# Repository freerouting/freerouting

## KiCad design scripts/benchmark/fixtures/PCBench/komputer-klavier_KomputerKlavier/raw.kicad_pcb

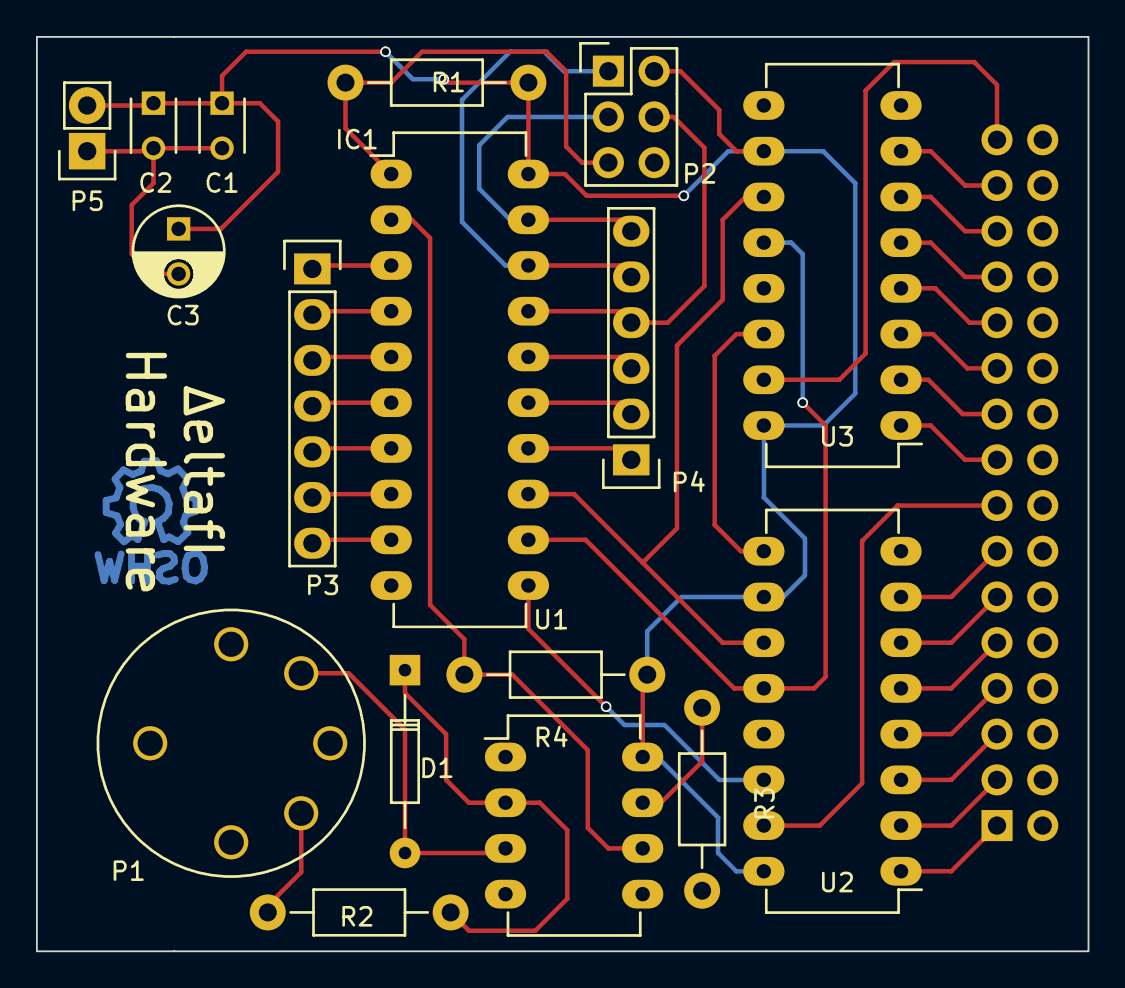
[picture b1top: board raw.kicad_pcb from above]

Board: 2 copper layers, 58.4 x 50.8 mm, 18 parts (1 on the bottom side), 41 nets.

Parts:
C1, C2: 100nf; C_Disc_D3_P2.5
C3: 1uf; C_Radial_D5_L6_P2.5
D1: 1N4148; Diode_DO-35_SOD27_Horizontal_RM10
IC1: ATTINY4313-P; DIP-20_W7.62mm_LongPads
P1: DIN_5
P2: CONN_02X03; Pin_Header_Straight_2x03
P3: CONN_01X07; Pin_Header_Straight_1x07
P4: CONN_01X06; Pin_Header_Straight_1x06
P5: CONN_01X02; Pin_Header_Straight_1x02
P6: CONN_02X16; Pin_Header_Straight_2x16
R1: 10k; Resistor_Horizontal_RM10mm
R2: 220; Resistor_Horizontal_RM10mm
R3: 1k; Resistor_Horizontal_RM10mm
R4: 470; Resistor_Horizontal_RM10mm
U1: 6N136; DIP-8_W7.62mm_LongPads
U2, U3: 74HC595; DIP-16_W7.62mm_LongPads

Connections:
GND: C1.2, C2.2, C3.2, IC1.10, P2.6, P5.1, P6.2, P6.4, P6.6, P6.8, P6.10, P6.12, P6.14, P6.16, P6.18, P6.20, P6.22, P6.24, P6.26, P6.28, P6.30, P6.32, R3.2, U1.5, U2.8, U2.13, U3.8, U3.13
unnamed: D1.1, R2.1, U1.2
unnamed: D1.2, P1.5, U1.3
unnamed: IC1.1, P2.5, R1.2
unnamed: IC1.2, R4.2, U1.6
unnamed: IC1.3, P3.1
unnamed: IC1.4, P3.2
unnamed: IC1.5, P3.3
unnamed: IC1.6, P3.4
unnamed: IC1.7, P3.5
unnamed: IC1.8, P3.6
unnamed: IC1.9, P3.7
unnamed: IC1.11, U2.14
unnamed: IC1.12, U2.12, U3.12
unnamed: IC1.13, U2.11, U3.11
unnamed: IC1.14, P4.1
unnamed: IC1.15, P4.2
unnamed: IC1.16, P4.3
unnamed: IC1.17, P2.4, P4.4
unnamed: IC1.18, P2.1, P4.5
unnamed: IC1.19, P2.3, P4.6
unnamed: P1.4, R2.2
unnamed: P6.1, U2.1
unnamed: P6.3, U2.2
unnamed: P6.5, U2.3
unnamed: P6.7, U2.4
unnamed: P6.9, U2.5
unnamed: P6.11, U2.6
unnamed: P6.13, U2.7
unnamed: P6.15, U2.15
unnamed: P6.17, U3.1
unnamed: P6.19, U3.2
unnamed: P6.21, U3.3
unnamed: P6.23, U3.4
unnamed: P6.25, U3.5
unnamed: P6.27, U3.6
unnamed: P6.29, U3.7
unnamed: P6.31, U3.15
unnamed: R3.1, U1.7
unnamed: U2.9, U3.14
VCC: C1.1, C2.1, C3.1, IC1.20, P2.2, P5.2, R1.1, R4.1, U1.8, U2.10, U2.16, U3.10, U3.16

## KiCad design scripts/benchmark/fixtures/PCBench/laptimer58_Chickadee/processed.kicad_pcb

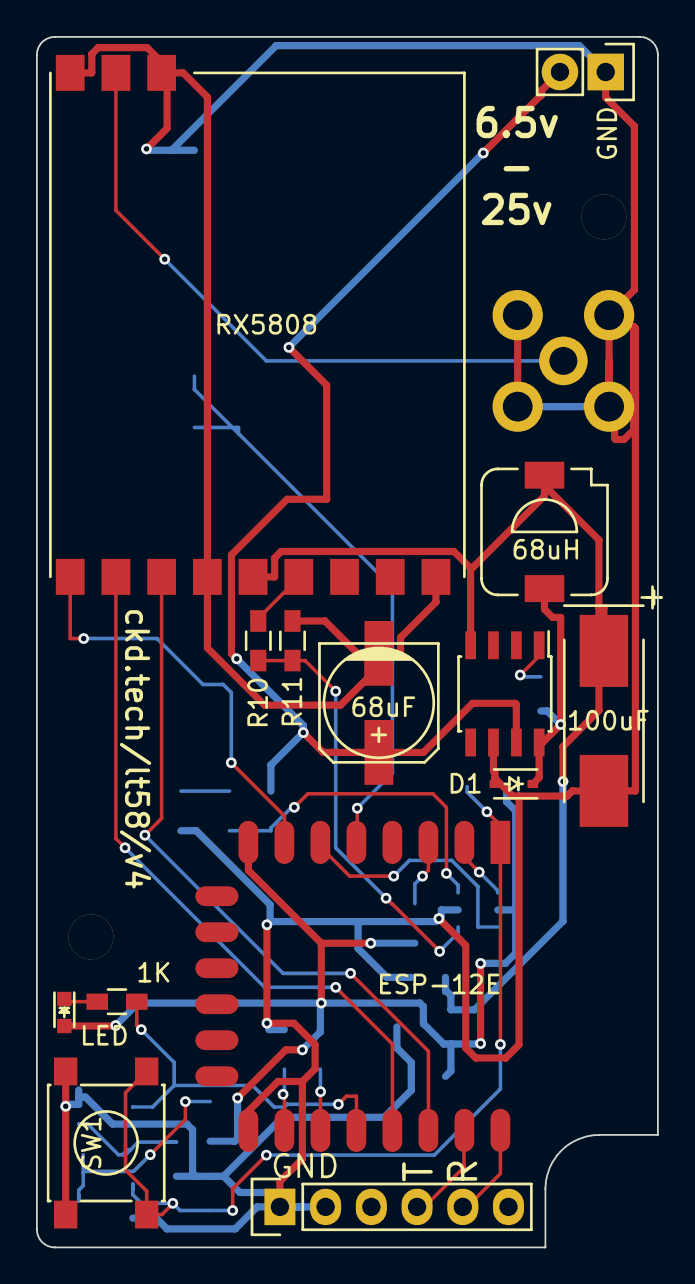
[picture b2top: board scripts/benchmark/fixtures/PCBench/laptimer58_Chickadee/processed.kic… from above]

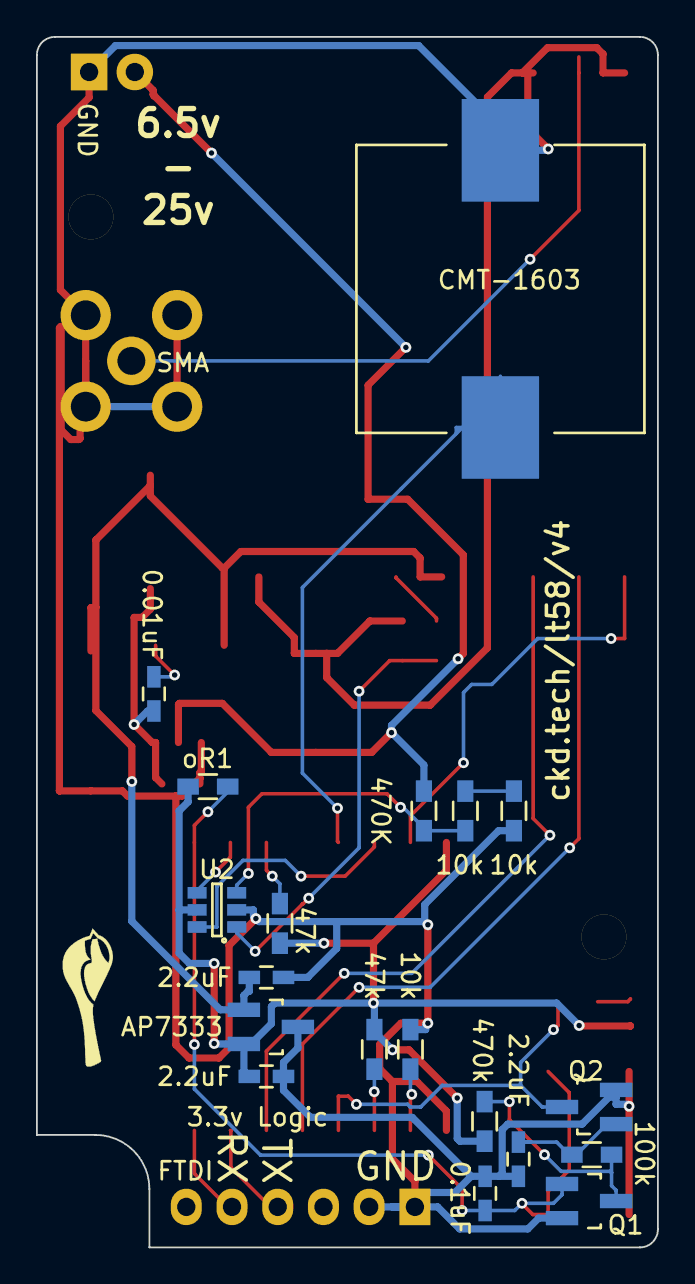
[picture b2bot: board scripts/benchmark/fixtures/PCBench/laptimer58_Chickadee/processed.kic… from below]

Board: 2 copper layers, 34.5 x 67.2 mm, 34 parts (19 on the bottom side), 27 nets.

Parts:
C1: 0.1uF; C_0603_HandSoldering
C2, C3, C4: 2.2uF; C_0603_HandSoldering
CB1: 0.01uF; C_0603_HandSoldering
Cin1: 68uF; c_elec_6.3x7.7
Cout1: 100uF; TantalC_SizeD_EIA-7343_HandSoldering
D1: SD103BWS-TP; SOD-323
D2: LED; LED-0603
J1: SMA; SMA-Jack-Straight
L1: 68uH; SLF7032
LS1: CMT-1603; CMT-1603-SMT
P1: FTDI; Pin_Header_Straight_1x06
P2: CONN_01X02; Pin_Header_Straight_1x02
Q1, Q2: Q_NMOS_GSD; SOT-23_Handsoldering
R1: 470k; R_0603_HandSoldering
R2: 100k; R_0603_HandSoldering
R3, R5: 47k; R_0603_HandSoldering
R4: 1K; R_0603_HandSoldering
R6, R8, R9, R11: 10k; R_0603_HandSoldering
R7: 470K; R_0603_HandSoldering
R10: 1k; R_0603_HandSoldering
RF1: RX5808; rx5808
SW1: SW_PUSH; SW_SPST_PTS645
U1: ESP-12E
U2: 74LVC1G3157; SOT-23-6
U3: LM2674M-3.3; SOIC-8_3.9x4.9mm_Pitch1.27mm
U4: AP7333; SOT-23_Handsoldering
oR1: 10k; R_0603_HandSoldering

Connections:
+3V3: C4.1, D2.2, R1.1, R3.2, R5.1, U1.8, U2.5, U4.2, oR1.1
+5V: C3.1, Cout1.1, L1.1, RF1.8, U3.4, U4.1
+BATT: Cin1.1, P2.2, R7.1, U3.7
/5V/3V3 Regulator/5uf: CB1.2, D1.1, L1.2, U3.8
/ADC_SELECT: U1.6, U2.6
/CLK: RF1.6, U1.20
/DATA: RF1.4, U1.7
/ESP-Reset/GPIO0: Q2.3, R4.2, U1.18
/ESP-Reset/RESET: C1.1, Q1.1, SW1.2, U1.1, oR1.2
/LE: RF1.5, U1.19
/RFIN: J1.1, RF1.2
/RSSI: R10.1, RF1.9
/RXI: P1.5, U1.22
/SHARED_ADC: U1.2, U2.4
/TXO: P1.4, U1.21
GNDPWR: C1.2, C2.2, C3.2, C4.2, Cin1.2, Cout1.2, D1.2, J1.2, J1.3, J1.4, J1.5, LS1.2, P1.1, P1.2, P2.1, Q1.2, Q2.2, R6.1, R9.2, R11.2, RF1.1, RF1.3, RF1.7, RF1.12, SW1.1, U1.15, U2.2, U3.6, U4.3
unnamed: C2.1, Q2.1, R2.1
unnamed: CB1.1, U3.1
unnamed: D2.1, R4.1
unnamed: LS1.1, U1.5
unnamed: Q1.3, R1.2, R2.2
unnamed: R3.1, U1.3
unnamed: R5.2, U1.17
unnamed: R6.2, U1.16
unnamed: R7.2, R8.1, U2.3
unnamed: R8.2, R9.1
unnamed: R10.2, R11.1, U2.1

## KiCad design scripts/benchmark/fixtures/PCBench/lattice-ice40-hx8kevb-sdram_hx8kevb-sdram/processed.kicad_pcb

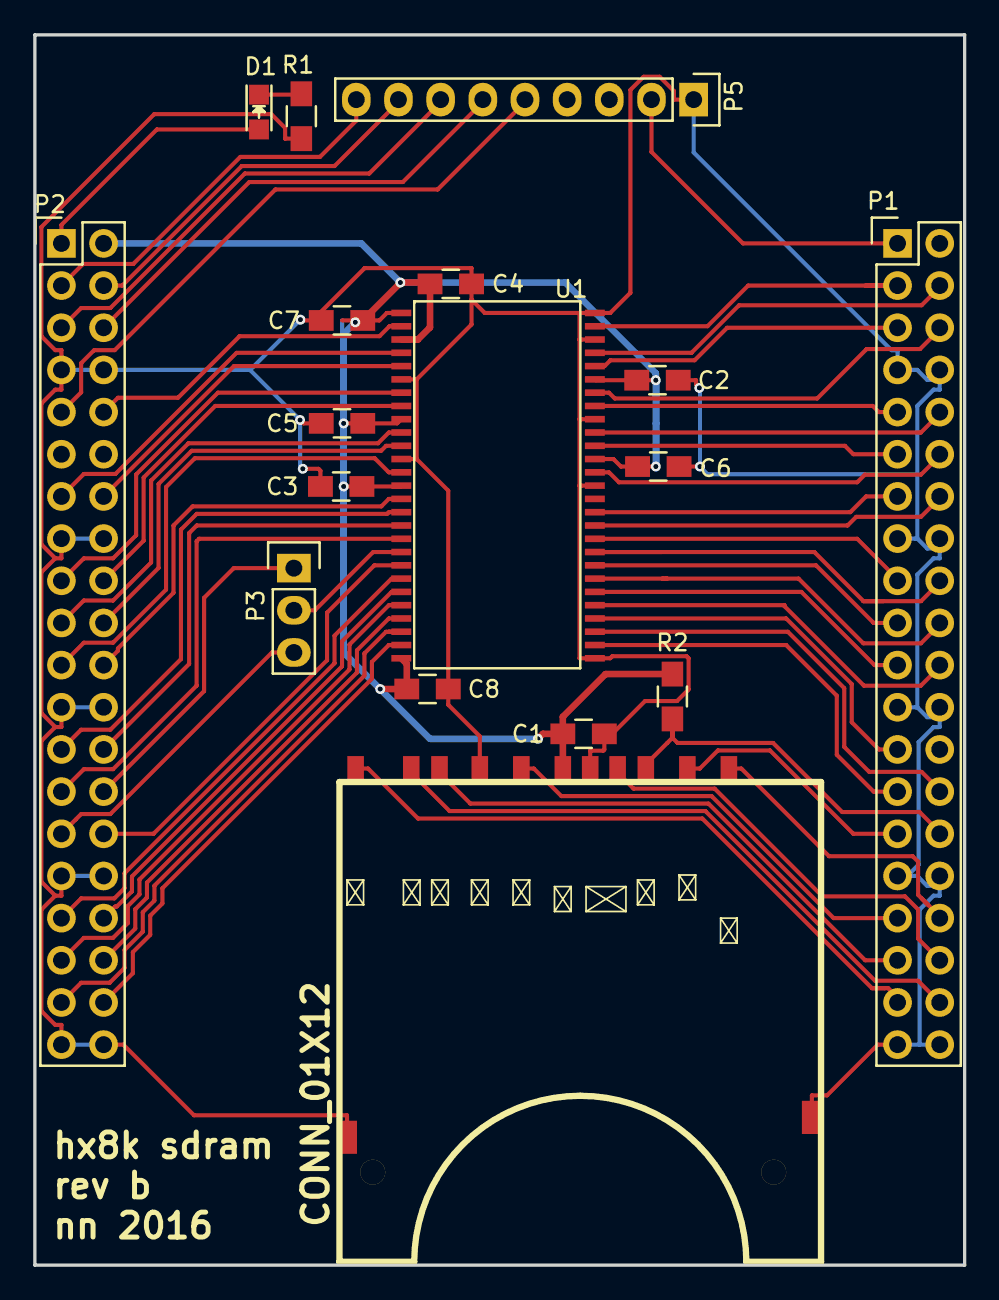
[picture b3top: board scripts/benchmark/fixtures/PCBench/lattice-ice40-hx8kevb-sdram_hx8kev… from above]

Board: 2 copper layers, 56.0 x 74.1 mm, 17 parts (0 on the bottom side), 59 nets.

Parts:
C1, C2, C3, C4, C5, C6, C7, C8: C; C_0805_HandSoldering
D1: LED; LED_0805
P1, P2: CONN_02X20; Pin_Header_Straight_2x20
P3: CONN_01X03; Pin_Header_Straight_1x03
P4: CONN_01X12; SD_CARD_10100
P5: CONN_01X09; Pin_Header_Straight_1x09
R1, R2: R; R_0805_HandSoldering
U1: AS4C16M16; TSOP-54

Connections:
+3V3: C1.1, C2.1, C3.1, C4.1, C5.2, C6.2, C7.2, C8.1, P2.2, P4.4, R2.1, U1.1, U1.3, U1.9, U1.14, U1.27, U1.43, U1.49
/A0: P2.35, U1.23
/A1: P2.36, U1.24
/A2: P2.37, U1.25
/A3: P2.38, U1.26
/A4: P1.27, U1.29
/A5: P1.28, U1.30
/A6: P1.25, U1.31
/A7: P1.22, U1.32
/A8: P1.21, U1.33
/A9: P1.20, U1.34
/A10: P2.34, U1.22
/A11: P1.19, U1.35
/A12: P1.18, U1.36
/BA0: P2.30, U1.20
/BA1: P2.33, U1.21
/CAS: P2.26, U1.17
/CKE: P1.17, U1.37
/CLK: P1.14, U1.38
/CS: P3.2, U1.19
/CS1: P2.28, P3.1
/CS2: P2.29, P3.3
/DQ0: P2.10, U1.2
/DQ1: P2.13, U1.4
/DQ2: P2.14, U1.5
/DQ3: P2.17, U1.7
/DQ4: P2.18, U1.8
/DQ5: P2.19, U1.10
/DQ6: P2.20, U1.11
/DQ7: P2.21, U1.13
/DQ8: P1.12, U1.42
/DQ9: P1.11, U1.44
/DQ10: P1.10, U1.45
/DQ11: P1.9, U1.47
/DQ12: P1.6, U1.48
/DQ13: P1.5, U1.50
/DQ14: P1.4, U1.51
/DQ15: P1.3, U1.53
/GPIO1: P2.3, P5.9
/GPIO2: P2.4, P5.8
/GPIO3: P2.5, P5.7
/GPIO4: P2.6, P5.6
/GPIO5: P2.9, P5.5
/GPIO8: P1.1, P5.2
/LDQM: P2.22, U1.15
/LED: D1.2, P2.1
/RAS: P2.27, U1.18
/SD_CD: P1.36, P4.10
/SD_CLK: P1.33, P4.5
/SD_CMD: P1.30, P4.2, R2.2
/SD_D0: P1.35, P4.7
/SD_D1: P1.38, P4.8
/SD_D2: P1.34, P4.9
/SD_D3: P1.29, P4.1
/SD_WP: P1.37, P4.11
/UDQM: P1.13, U1.39
/WE: P2.25, U1.16
GND: C1.2, C2.2, C3.2, C4.2, C5.1, C6.1, C7.1, C8.2, P1.7, P1.8, P1.15, P1.16, P1.23, P1.24, P1.31, P1.32, P1.39, P1.40, P2.7, P2.8, P2.15, P2.16, P2.23, P2.24, P2.31, P2.32, P2.39, P2.40, P4.3, P4.6, P4.12, P5.1, R1.2, U1.6, U1.12, U1.28, U1.41, U1.46, U1.52, U1.54
unnamed: D1.1, R1.1
